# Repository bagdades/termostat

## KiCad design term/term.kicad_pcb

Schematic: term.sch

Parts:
BT1: Battery; BatteryHolder_ComfortableElectronic_CH273-2450_1x2450
C1, C2, C3, C4, C5, C6, C7, C8, C10: 100n; C_0805_2012Metric
C9, C11: 22p; C_0805_2012Metric
J1, J2, J3: Conn_01x03_Male
J4: Conn_ARM_JTAG_SWD_10; IDC-Header_2x05_P2.54mm_Vertical
R1: 1k; R_0805_2012Metric
R2, R6, R7: 4k7; R_0805_2012Metric
R3: 10; R_1210_3225Metric
R4, R5: 100k; R_0805_2012Metric
RV1: 10k; Potentiometer_ACP_CA9-V10_Vertical
U1: 74HC595; SOIC-16_3.9x9.9mm_P1.27mm
U2: WG12864A; PinHeader_1x20_P2.54mm_Vertical
U3: STM32F103C8Tx; LQFP-48_7x7mm_P0.5mm
U4: FM24C64B; SOIC-8_3.9x4.9mm_P1.27mm
Y1: 8MHz; Resonator_SMD_muRata_CSTxExxV-3Pin_3.0x1.1mm
Y2: 32678; Crystal_SMD_3215-2Pin_3.2x1.5mm

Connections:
/JTCK: J4.4 (SWDCLK/TCK), U3.37 (PA14)
/JTDI: J4.8 (NC/TDI), U3.38 (PA15)
/JTDO: J4.6 (SWO/TDO), U3.39 (PB3)
/JTMS: J4.2 (SWDIO/TMS), U3.34 (PA13)
/KEY_DOWN: U3.13 (PA3)
/KEY_LEFT: U3.14 (PA4)
/KEY_RIGHT: U3.15 (PA5)
/KEY_UP: U3.12 (PA2)
/LCD_CLK: U1.12 (RCLK), U3.25 (PB12)
/LCD_CS1: U2.15 (CS1), U3.45 (PB8)
/LCD_CS2: U2.16 (CS2), U3.46 (PB9)
/LCD_DATA: U1.14 (SER), U3.28 (PB15)
/LCD_DI: U2.4 (D/I), U3.22 (PB11)
/LCD_E: U2.6 (E), U3.27 (PB14)
/LCD_RST: U2.17 (~RES), U3.21 (PB10)
/LCD_SHIFT: U1.11 (SRCLK), U3.26 (PB13)
/NRESET: C10.1, J4.10 (~RESET~), R4.2, U3.7 (NRST)
/OW: J1.2, J2.2, J3.2, R2.1, U3.17 (PA7)
/SCL: R7.2, U3.42 (PB6), U4.6 (SCL)
/SDA: R6.2, U3.43 (PB7), U4.5 (SDA)
/USART1_RX: U3.31 (PA10)
/USART1_TX: U3.30 (PA9)
GND: BT1.2 (-), C1.2, C2.2, C3.2, C4.2, C5.2, C6.2, C7.2, C8.2, C9.1, C10.2, C11.2, J1.3, J2.3, J3.3, J4.3 (GND), J4.5 (GND), J4.9 (GNDDetect), R3.2, R5.2, U1.8 (GND), U1.13 (~OE), U2.1 (Vss), U2.5 (R/W), U3.8 (VSSA), U3.23 (VSS), U3.35 (VSS), U3.47 (VSS), U4.1 (A0), U4.2 (A1), U4.3 (A2), U4.4 (VSS), U4.7 (WP), Y1.2
unnamed: BT1.1 (+), U3.1 (VBAT)
unnamed: C9.2, U3.3 (PC14), Y2.2
unnamed: C11.1, U3.4 (PC15), Y2.1
unnamed: J1.1, J2.1, J3.1
unnamed: R1.2, U1.10 (~SRCLR)
unnamed: R3.1, U2.20 (K)
unnamed: R5.1, U3.44 (BOOT0)
unnamed: RV1.2, U2.3 (V0)
unnamed: RV1.3, U2.18 (Vout)
unnamed: U1.1 (QB), U2.8 (DB1)
unnamed: U1.2 (QC), U2.9 (DB2)
unnamed: U1.3 (QD), U2.10 (DB3)
unnamed: U1.4 (QE), U2.11 (DB4)
unnamed: U1.5 (QF), U2.12 (DB5)
unnamed: U1.6 (QG), U2.13 (DB6)
unnamed: U1.7 (QH), U2.14 (DB7)
unnamed: U1.15 (QA), U2.7 (DB0)
unnamed: U3.5 (PD0), Y1.1
unnamed: U3.6 (PD1), Y1.3
VCC: R1.1, RV1.1, U1.16 (VCC), U2.2 (Vdd), U2.19 (A)

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
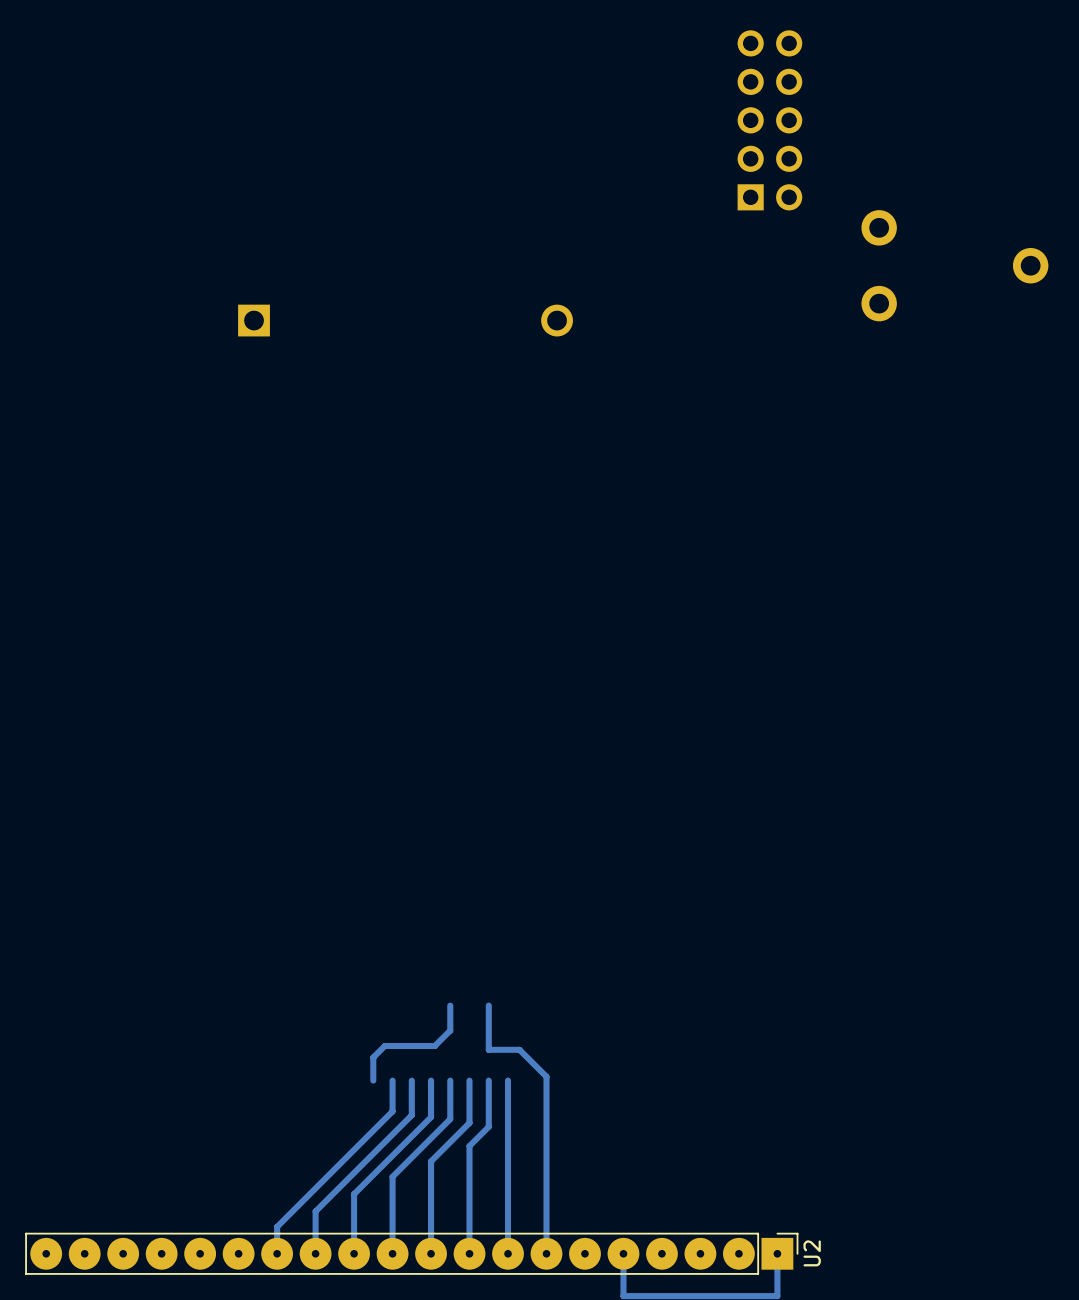
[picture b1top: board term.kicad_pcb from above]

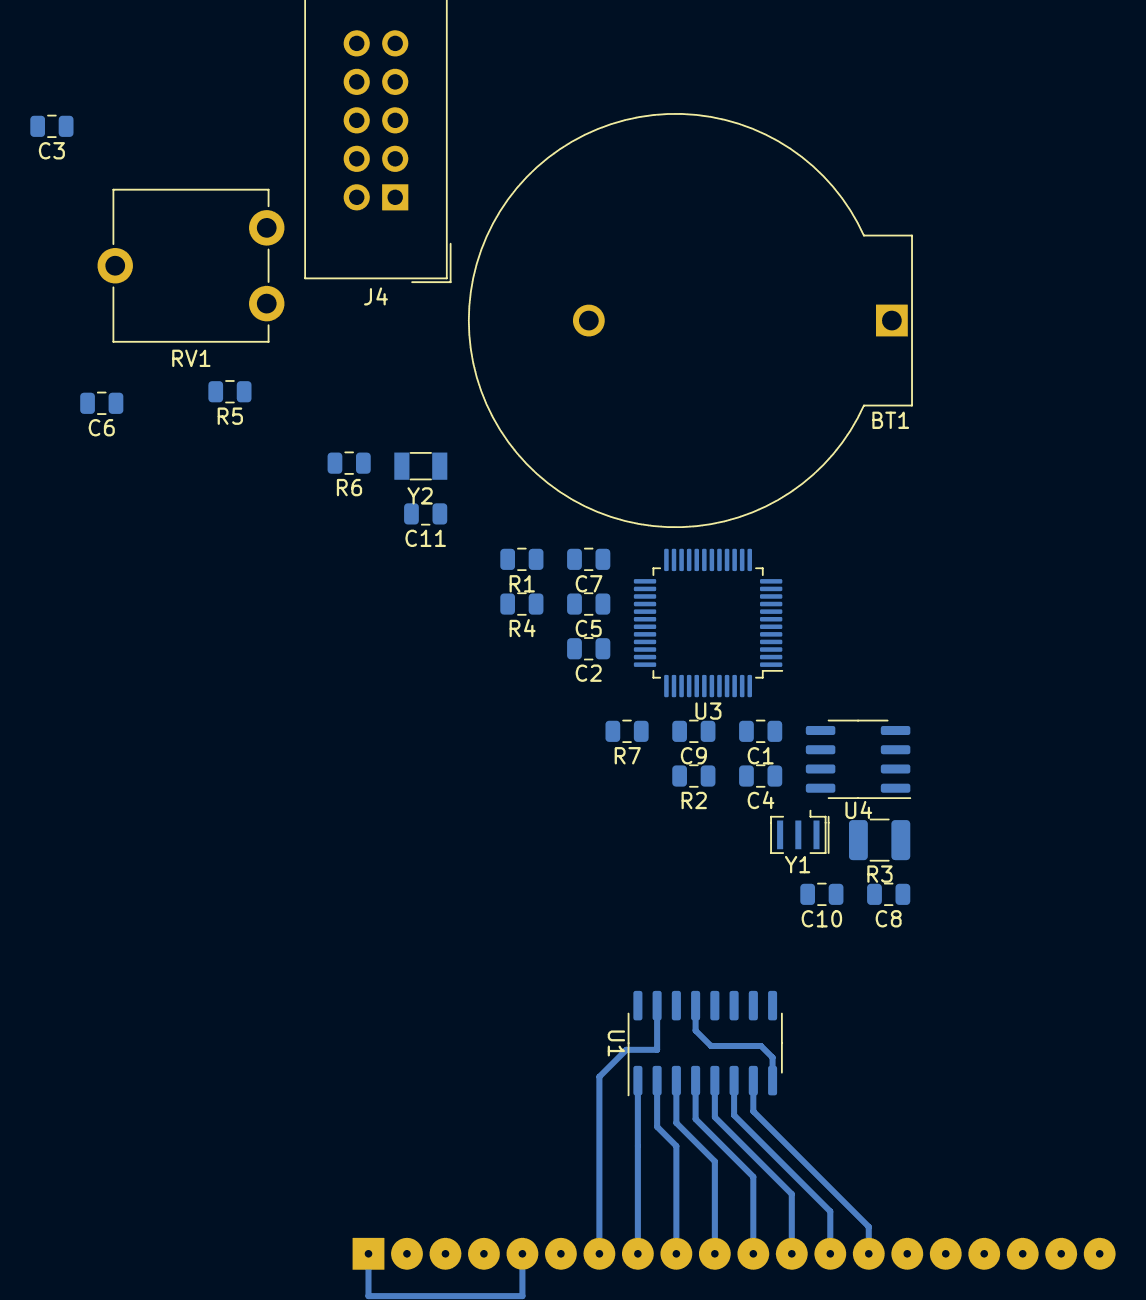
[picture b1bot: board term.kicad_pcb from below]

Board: 2 copper layers, 27 parts (26 on the bottom side), 37 nets.

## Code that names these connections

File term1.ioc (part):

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Mcu.Name=STM32F103C(8-B)Tx
Mcu.Package=LQFP48
Mcu.UserName=STM32F103C8Tx
PA0-WKUP.GPIOParameters=GPIO_Speed,GPIO_Label
PA0-WKUP.GPIO_Label=LED1
PA0-WKUP.GPIO_Speed=GPIO_SPEED_FREQ_MEDIUM
PA0-WKUP.Signal=GPIO_Output
PA1.GPIOParameters=GPIO_Speed,GPIO_Label
PA1.GPIO_Label=LED2
PA1.GPIO_Speed=GPIO_SPEED_FREQ_MEDIUM
PA1.Signal=GPIO_Output
PA10.Mode=Asynchronous
PA10.Signal=USART1_RX
PA13.Mode=Serial_Wire
PA13.Signal=SYS_JTMS-SWDIO
PA14.Mode=Serial_Wire
PA14.Signal=SYS_JTCK-SWCLK
PA2.GPIOParameters=GPIO_PuPd,GPIO_Label
PA2.GPIO_Label=KEY_UP
PA2.GPIO_PuPd=GPIO_PULLUP
PA2.Signal=GPIO_Input
PA3.GPIOParameters=GPIO_PuPd,GPIO_Label
PA3.GPIO_Label=KEY_DOWN
PA3.GPIO_PuPd=GPIO_PULLUP
PA3.Signal=GPIO_Input
PA4.GPIOParameters=GPIO_PuPd,GPIO_Label
PA4.GPIO_Label=KEY_LEFT
PA4.GPIO_PuPd=GPIO_PULLUP
PA4.Signal=GPIO_Input
PA5.GPIOParameters=GPIO_PuPd,GPIO_Label
PA5.GPIO_Label=KEY_RIGHT
PA5.GPIO_PuPd=GPIO_PULLUP
PA5.Signal=GPIO_Input
PA6.GPIOParameters=GPIO_Speed,GPIO_Label
PA6.GPIO_Label=LED3
PA6.GPIO_Speed=GPIO_SPEED_FREQ_MEDIUM
PA6.Signal=GPIO_Output
PA7.Signal=GPIO_Input
PA9.Mode=Asynchronous
PA9.Signal=USART1_TX
PB10.GPIOParameters=GPIO_Speed,PinState,GPIO_PuPd,GPIO_Label
PB10.GPIO_Label=LCD_RST
PB10.GPIO_PuPd=GPIO_PULLUP
PB10.GPIO_Speed=GPIO_SPEED_FREQ_HIGH
PB10.PinState=GPIO_PIN_SET
PB10.Signal=GPIO_Output
PB11.GPIOParameters=GPIO_Speed,GPIO_PuPd,GPIO_Label
PB11.GPIO_Label=LCD_DI
PB11.GPIO_PuPd=GPIO_PULLUP
PB11.GPIO_Speed=GPIO_SPEED_FREQ_HIGH
PB11.Signal=GPIO_Output
PB12.GPIOParameters=GPIO_Speed,GPIO_PuPd,GPIO_Label
PB12.GPIO_Label=LCD_CLK
PB12.GPIO_PuPd=GPIO_PULLUP
PB12.GPIO_Speed=GPIO_SPEED_FREQ_HIGH
PB12.Signal=GPIO_Output
PB13.GPIOParameters=GPIO_Speed,GPIO_PuPd,GPIO_Label
PB13.GPIO_Label=LCD_SHIFT
PB13.GPIO_PuPd=GPIO_PULLUP
PB13.GPIO_Speed=GPIO_SPEED_FREQ_HIGH
PB13.Signal=GPIO_Output
PB14.GPIOParameters=GPIO_Speed,GPIO_PuPd,GPIO_Label
PB14.GPIO_Label=LCD_E
PB14.GPIO_PuPd=GPIO_PULLUP
PB14.GPIO_Speed=GPIO_SPEED_FREQ_HIGH
PB14.Signal=GPIO_Output
PB15.GPIOParameters=GPIO_Speed,GPIO_PuPd,GPIO_Label
PB15.GPIO_Label=LCD_DATA
PB15.GPIO_PuPd=GPIO_PULLUP
PB15.GPIO_Speed=GPIO_SPEED_FREQ_HIGH
PB15.Signal=GPIO_Output
PB6.Mode=I2C
PB6.Signal=I2C1_SCL
PB7.Mode=I2C
PB7.Signal=I2C1_SDA
PB8.GPIOParameters=GPIO_Speed,GPIO_PuPd,GPIO_Label
PB8.GPIO_Label=LCD_CS1
PB8.GPIO_PuPd=GPIO_PULLUP
PB8.GPIO_Speed=GPIO_SPEED_FREQ_HIGH
PB8.Signal=GPIO_Output
PB9.GPIOParameters=GPIO_Speed,GPIO_PuPd,GPIO_Label
PB9.GPIO_Label=LCD_CS2
PB9.GPIO_PuPd=GPIO_PULLUP
PB9.GPIO_Speed=GPIO_SPEED_FREQ_HIGH
PB9.Signal=GPIO_Output
PC14-OSC32_IN.Mode=LSE-External-Oscillator
PC14-OSC32_IN.Signal=RCC_OSC32_IN
PC15-OSC32_OUT.Mode=LSE-External-Oscillator
PC15-OSC32_OUT.Signal=RCC_OSC32_OUT
PD0-OSC_IN.Mode=HSE-External-Oscillator
PD0-OSC_IN.Signal=RCC_OSC_IN
PD1-OSC_OUT.Mode=HSE-External-Oscillator
PD1-OSC_OUT.Signal=RCC_OSC_OUT
RCC.SYSCLKFreq_VALUE=72000000
RCC.SYSCLKSource=RCC_SYSCLKSOURCE_PLLCLK
board=custom

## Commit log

2019-12-01 Add setup date, time key functions
2019-12-08 Extend menu setting
2019-12-15 Expand menu Setting, start kicad project
2019-12-16 Add function TermGetWorkTemp
2019-12-19 Add setting work days of week
2019-12-20 Add eeprom functions, i2c functions, save and restore data
2020-01-01 Continue schematic draw
2020-01-21 Add kicad project with stm32 module
